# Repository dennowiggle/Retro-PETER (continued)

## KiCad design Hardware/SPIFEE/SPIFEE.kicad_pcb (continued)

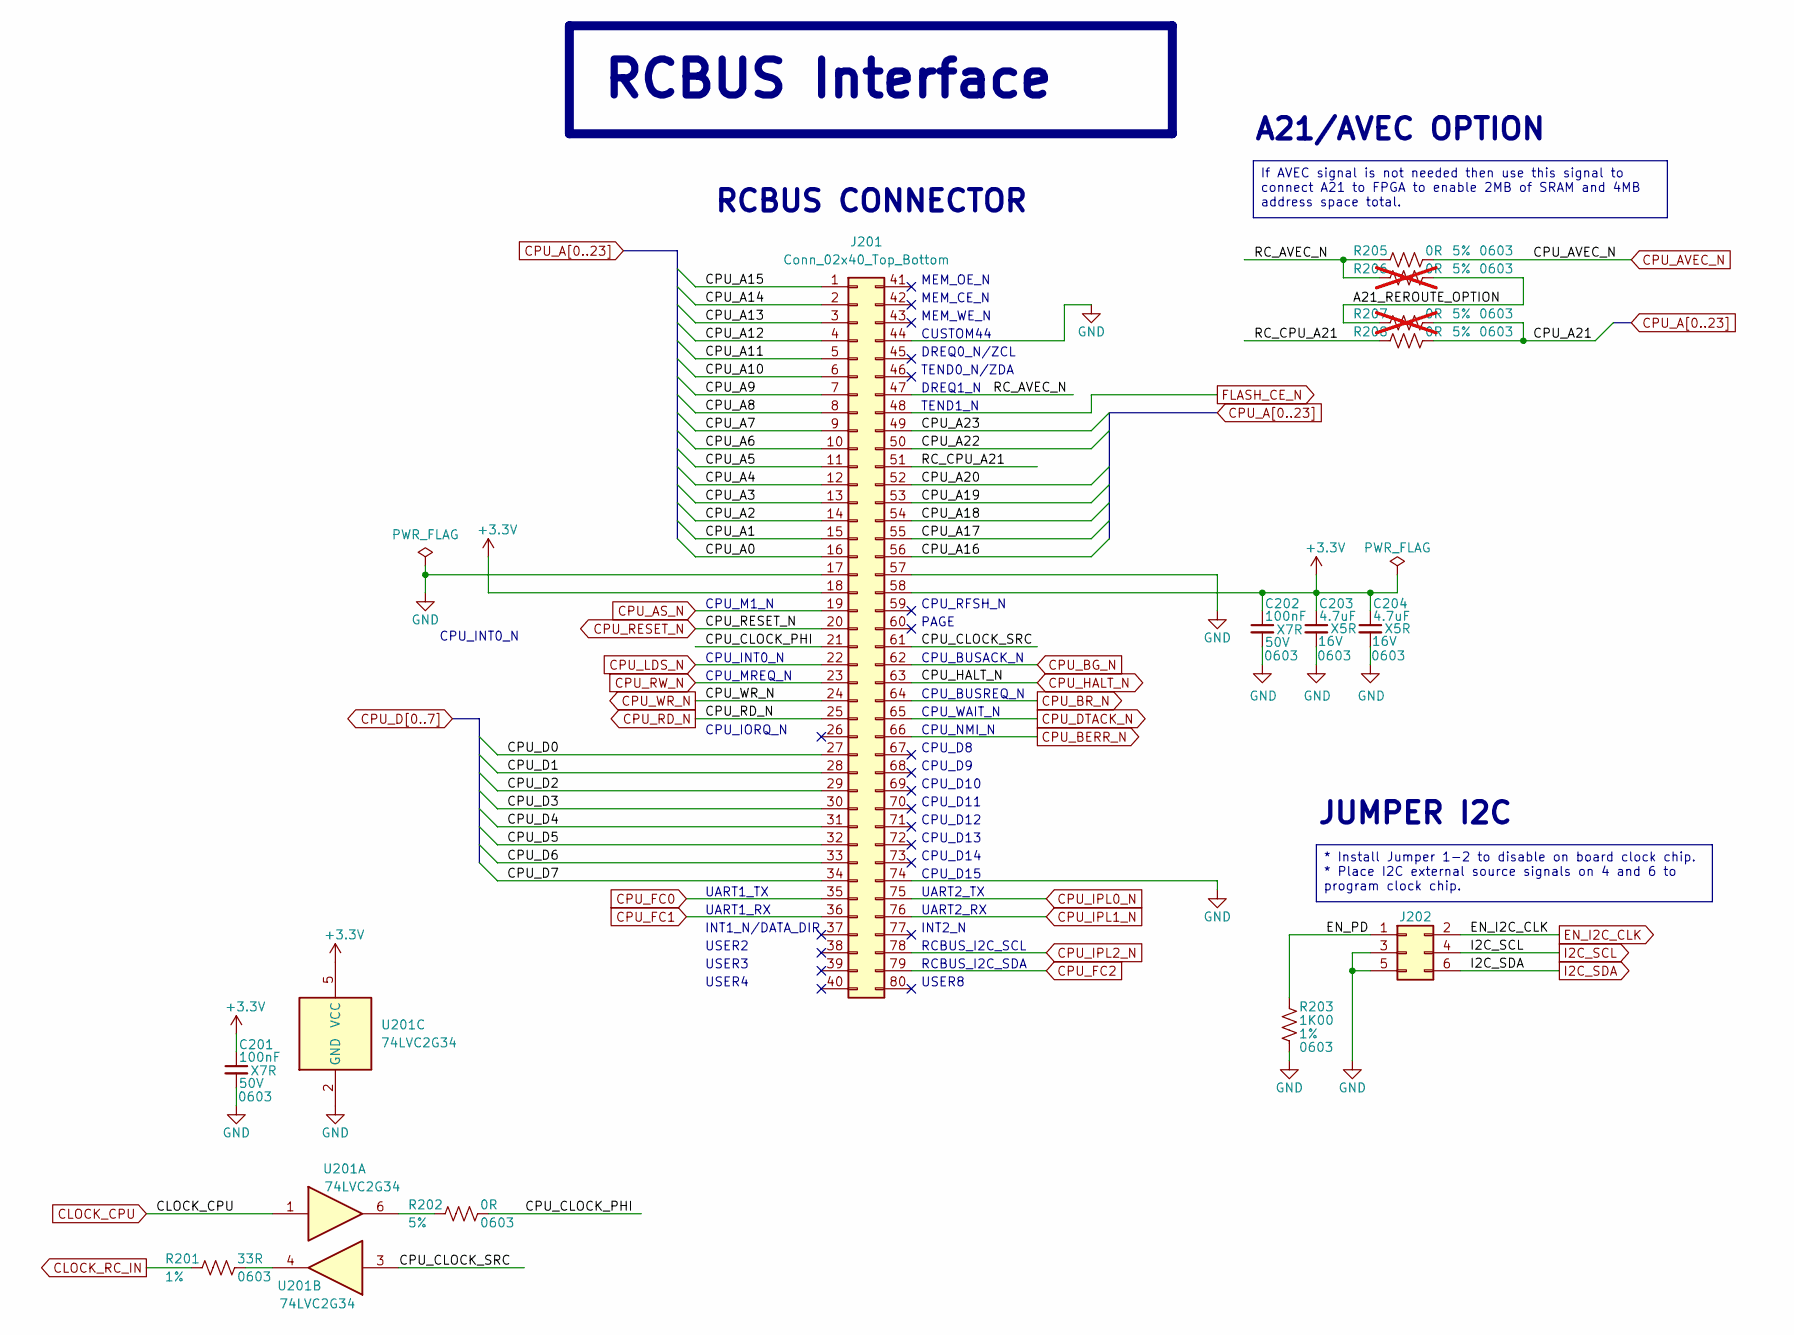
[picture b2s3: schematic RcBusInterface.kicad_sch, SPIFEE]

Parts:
C201, C202: 100nF; C_0603_1608Metric; Voltage 50V; Tolerance 10%; MPN CC0603KRX7R9BB104; Digikey 311-1344-1-ND
C203, C204: 4.7uF; C_0603_1608Metric; Voltage 16V; Tolerance 10%; MPN CL10A475KO8NNNC; Digikey 1276-1784-1-ND
J201: Conn_02x40_Top_Bottom; RCBUS_PinHeader_2x40_P2.54mm_Horizontal; MPN PH2RA-80-UA; Digikey 2057-PH2RA-80-UA-ND
J202: Conn_02x03; PinHeader_2x03_P2.54mm_Vertical; MPN PH2-06-UA; Digikey 2057-PH2-06-UA-ND
R201: 33R; R_0603_1608Metric; Tolerance 1%; MPN RC0603FR-0733RL; Digikey 13-RC0603FR-0733RLCT-ND
R202, R205, R208: 0R; R_0603_1608Metric; Tolerance 5%; MPN RC0603JR-070RL; Digikey 311-0.0GRCT-ND
R203: 1K00; R_0603_1608Metric; Tolerance 1%; MPN RC0603FR-071KL; Digikey 311-1.00KHRCT-ND
R206, R207: 0R; R_0603_1608Metric; Tolerance 5%; MPN RC0603JR-070RL; Digikey 311-0.0GRCT-ND; not fitted
U201: 74LVC2G34; SOT-363_SC-70-6; MPN 74LVC2G34GW,125; Digikey 1727-4219-1-ND

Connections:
+3.3V: C201.1, C202.1, C203.1, C204.1, J201.18, J201.58, U201.5 (VCC); also elsewhere on the board
/RcBusInterface/A21_REROUTE_OPTION: R206.2, R207.1
/RcBusInterface/CPU_CLOCK_PHI: J201.21, R202.2
/RcBusInterface/CPU_CLOCK_SRC: J201.61, U201.3
/RcBusInterface/EN_PD: J202.1, R203.1
/RcBusInterface/RC_AVEC_N: J201.47, R205.1, R206.1
/RcBusInterface/RC_CPU_A21: J201.51, R208.1
CLOCK_CPU: U201.1; also elsewhere on the board
CLOCK_RC_IN: R201.1; also elsewhere on the board
CPU_A0: J201.16; also elsewhere on the board
CPU_A1: J201.15; also elsewhere on the board
CPU_A2: J201.14; also elsewhere on the board
CPU_A3: J201.13; also elsewhere on the board
CPU_A4: J201.12; also elsewhere on the board
CPU_A5: J201.11; also elsewhere on the board
CPU_A6: J201.10; also elsewhere on the board
CPU_A7: J201.9; also elsewhere on the board
CPU_A8: J201.8; also elsewhere on the board
CPU_A9: J201.7; also elsewhere on the board
CPU_A10: J201.6; also elsewhere on the board
CPU_A11: J201.5; also elsewhere on the board
CPU_A12: J201.4; also elsewhere on the board
CPU_A13: J201.3; also elsewhere on the board
CPU_A14: J201.2; also elsewhere on the board
CPU_A15: J201.1; also elsewhere on the board
CPU_A16: J201.56; also elsewhere on the board
CPU_A17: J201.55; also elsewhere on the board
CPU_A18: J201.54; also elsewhere on the board
CPU_A19: J201.53; also elsewhere on the board
CPU_A20: J201.52; also elsewhere on the board
CPU_A21: R207.2, R208.2; also elsewhere on the board
CPU_A22: J201.50; also elsewhere on the board
CPU_A23: J201.49; also elsewhere on the board
CPU_AS_N: J201.19; also elsewhere on the board
CPU_AVEC_N: R205.2; also elsewhere on the board
CPU_BERR_N: J201.66; also elsewhere on the board
CPU_BG_N: J201.62; also elsewhere on the board
CPU_BR_N: J201.64; also elsewhere on the board
CPU_D0: J201.27; also elsewhere on the board
CPU_D1: J201.28; also elsewhere on the board
CPU_D2: J201.29; also elsewhere on the board
CPU_D3: J201.30; also elsewhere on the board
CPU_D4: J201.31; also elsewhere on the board
CPU_D5: J201.32; also elsewhere on the board
CPU_D6: J201.33; also elsewhere on the board
CPU_D7: J201.34; also elsewhere on the board
CPU_DTACK_N: J201.65; also elsewhere on the board
CPU_FC0: J201.35; also elsewhere on the board
CPU_FC1: J201.36; also elsewhere on the board
CPU_FC2: J201.79; also elsewhere on the board
CPU_HALT_N: J201.63; also elsewhere on the board
CPU_IPL0_N: J201.75; also elsewhere on the board
CPU_IPL1_N: J201.76; also elsewhere on the board
CPU_IPL2_N: J201.78; also elsewhere on the board
CPU_LDS_N: J201.22; also elsewhere on the board
CPU_RD_N: J201.25; also elsewhere on the board
CPU_RESET_N: J201.20; also elsewhere on the board
CPU_RW_N: J201.23; also elsewhere on the board
CPU_WR_N: J201.24; also elsewhere on the board
EN_I2C_CLK: J202.2; also elsewhere on the board
FLASH_CE_N: J201.48; also elsewhere on the board
GND: C201.2, C202.2, C203.2, C204.2, J201.17, J201.44, J201.57, J201.74, J202.3, J202.5, R203.2, U201.2 (GND); also elsewhere on the board
I2C_SCL: J202.4; also elsewhere on the board
I2C_SDA: J202.6; also elsewhere on the board
unnamed: R201.2, U201.4
unnamed: R202.1, U201.6

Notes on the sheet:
MEM_OE_N
A21/AVEC OPTION
CPU_NMI_N
CPU_BUSACK_N
CPU_INT0_N
MEM_WE_N
CPU_RFSH_N
CPU_D11
RCBUS_I2C_SDA
RCBUS CONNECTOR
CPU_D15
TEND1_N
CPU_D8
CPU_D14
UART2_TX
CPU_D12
UART2_RX
USER2
INT2_N
USER4
JUMPER I2C
CPU_MREQ_N
USER3
CPU_M1_N
CPU_WAIT_N
RCBUS_I2C_SCL
TEND0_N/ZDA
INT1_N/DATA_DIR
MEM_CE_N
UART1_TX
CPU_D9
USER8
DREQ0_N/ZCL
UART1_RX
CPU_D13
PAGE
CPU_BUSREQ_N
CUSTOM44
DREQ1_N
CPU_IORQ_N

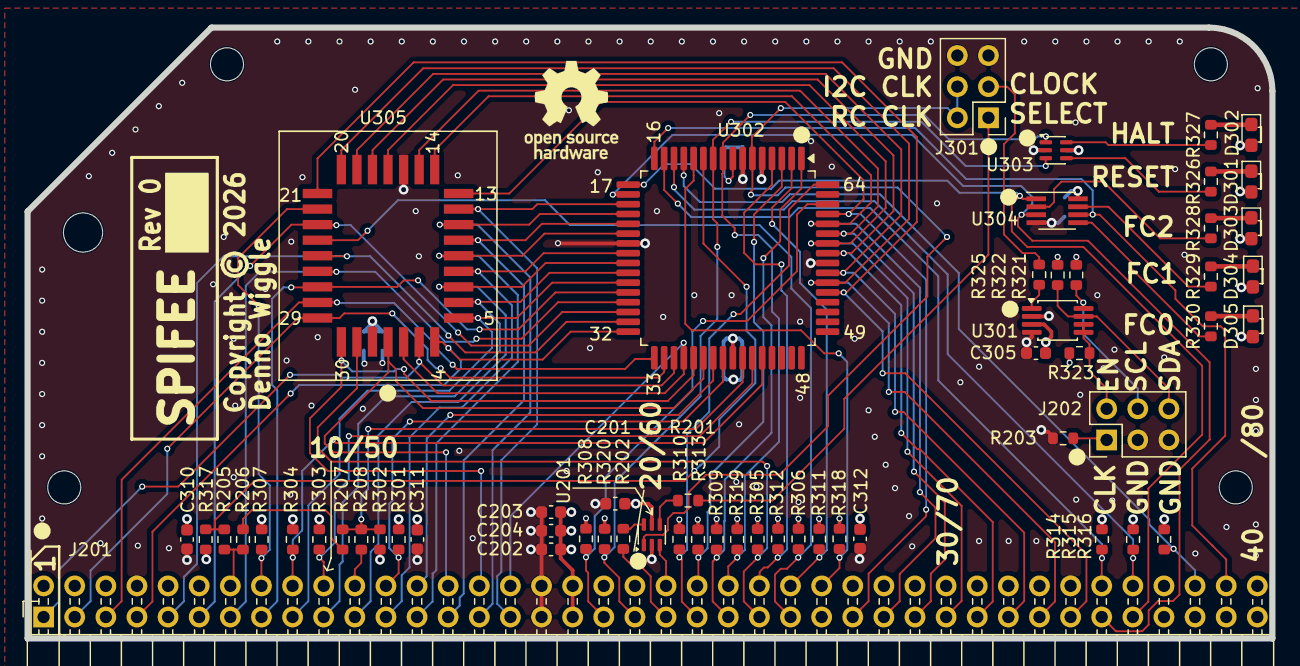
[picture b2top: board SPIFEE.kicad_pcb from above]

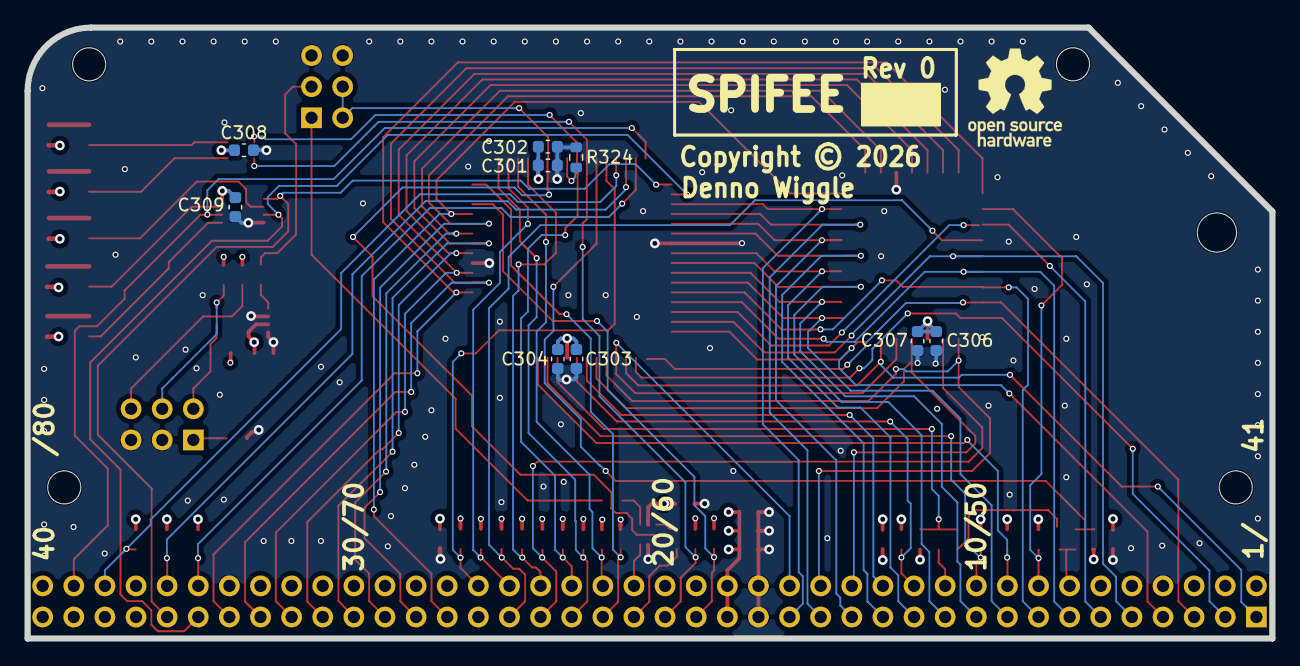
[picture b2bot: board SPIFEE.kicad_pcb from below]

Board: 4 copper layers, 101.6 x 49.9 mm, 74 parts (10 on the bottom side), 79 nets.

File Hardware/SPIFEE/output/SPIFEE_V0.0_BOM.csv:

"Reference","Value","Qty","DNP","Digikey","LCSC Part #","MPN","Manufacturer","Description"
"C201,C202,C301,C304,C305,C307,C308,C309,C310,C311,C312","100nF","11","","311-1344-1-ND","C14663","CC0603KRX7R9BB104","YAGEO","CAP CER 0.1UF 50V X7R 0603"
"R301,R302,R303,R304,R305,R306,R307,R308,R309,R310,R311,R312,R313,R314,R315,R316,R317,R318,R319,R320,R321,R322,R323","10K","23","","311-10.0KHRCT-ND","C98220","RC0603FR-0710KL","Yaego","RES 10K OHM 1% 1/10W 0603"
"R206,R207","0R","2","DNP","311-0.0GRCT-ND","C95177","RC0603JR-070RL","Yaego","RES 0 OHM 5% 1/10W 0603"
"R203,R326,R327,R328,R329,R330","1K00","6","","311-1.00KHRCT-ND","C22548","RC0603FR-071KL","Yaego","RES 1K OHM 1% 1/10W 0603"
"R202,R205,R208","0R","3","","311-0.0GRCT-ND","C95177","RC0603JR-070RL","Yaego","RES 0 OHM 5% 1/10W 0603"
"R201,R324,R325","33R","3","","13-RC0603FR-0733RLCT-ND","C108661","RC0603FR-0733RL","Yaego","RES 33 OHM 1% 1/10W 0603"
"C203,C204,C302,C303,C306","4.7uF","5","","1276-1784-1-ND","C19666","CL10A475KO8NNNC","Yaego","CAP CER 4.7UF 16V X5R 0603"
"U303","74LVC2G07","1","","1727-4121-1-ND","C24478","74LVC2G07GW,125","Nexperia","IC BUFF NON-INVERT 5.5V 6-TSSOP"
"U201","74LVC2G34","1","","1727-4219-1-ND","","74LVC2G34GW,125","Nexperia","IC BUFF NON-INVERT 5.5V 6-TSSOP"
"U302","MC68SEC000FU","1","","","","MC68SEC000FU20","Motorola","16/32-bit microprocessor, 16-bit external data bus, 23-bit external address bus (effectively 24-bit), QFP64"
"U305","SST39SF040-55","1","","SST39LF040-55-4C-NHE-ND","C645927","SST39LF040-55-4C-NHE","Microchip","IC FLASH 4MBIT 512KX8 PARALLEL 3V3 55ns PLCC32"
"D301,D302,D303,D304,D305","LED_LTST-S270KGKT","5","","160-1478-1-ND","C125113","LTST-S270KGKT","Lite-On Inc.","LED 571NM GREEN CLEAR CHIP 0603 R/A"
"U304","74LVC3G06","1","","31-74LVC3G06SS8-7CT-ND","C6089410","74LVC3G06SS8-7","Diodes Incorporated","IC INVERTER 3CH 3-INP 8SSOP"
"U301","DS1086LU+","1","","DS1086LU+-ND","C1519863","DS1086LU+","Analog Devices Inc./Maxim Integrated","IC I2C SS CLOCK GENERATOR uSOP8"
"J202,J301","Conn_02x03","2","","2057-PH2-06-UA-ND","","PH2-06-UA","Adam Tech","CONN HEADER VERT 6POS 2.54MM"
"J201","Conn_02x40_Top_Bottom","1","","2057-PH2RA-80-UA-ND","","PH2RA-80-UA","Adam Tech","CONN HEADER R/A 80POS 2.54MM"
"H1,H2,H3,H4,H5","MountingHole","5","","","","","",""

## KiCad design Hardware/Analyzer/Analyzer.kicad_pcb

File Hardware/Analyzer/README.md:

# ANALYZER
72 channel logic analyzer for RCBUS.

## Description
ANALYZER is a 72 channel logic analyzer in an RCBUS board form factor with 3 x Pi Pico modules. 

This design is a derivative work of John Winans [S-100 bus logic analyzer](https://github.com/johnwinans/2070-S-100-bus-analyzer) targeted for RCBUS instead of S-100 bus for use on the PETER project.

Both projects use the Dr Gusman [LogicAnalyzer software and firmware](https://github.com/gusmanb/logicanalyzer).

## Top View

## Bottom View

## ANALYZER Board Rev 0.0 Release Notes

1. The 'output' directory contains the BOM, netlist, and PDF schematic.

2. Board design used KiCad 10.0

3. Use sockets to mount the PICO's so that they are elevated above the board for anyone wanting to try WiFi.

## Notes for future
1. Consider using 3 x individual Pico 10K pull-down resistors for
  - TRIG_CHA, TRIG_CHB, TRIG_CHC instead of R302 2.2K on TRIG.

2. Consider replacing D201 with 3 schottky diodes to VSYS_A, VSYS_B, VSYS_B.
  - Provides option for manually sequencing power via each Pico USB connector.
  - Useful for getting same tty device name in Linux on each power on.

## Analyzer Board Pi Pico Channel Mapping to Signal and Pin Names
The [gusmanb software](https://github.com/gusmanb/logicanalyzer) only has the choice of 16 pins for trigger.

The table below has the middle PICO as the master. With the RCBUS backplane you can jumper the desired trigger signal to one of the unused pins. e.g. custom pin 41, analyzer channel 1.

 | Pico A       | Single A | Multi A | PETER Signal | RCBUS Pin | RCBUS Name  | 
 | ------------ | -------- | ------- | ------------ | --------- | ----------- |
 | GPIO_CHA_P2  | 1        | 25      | A15          | 1         | A15         | 
 | GPIO_CHA_P3  | 2        | 26      | A14          | 2         | A14         | 
 | GPIO_CHA_P4  | 3        | 27      | A13          | 3         | A13         | 
 | GPIO_CHA_P5  | 4        | 28      | DREQ0_N      | 45        | custom      | 
 | GPIO_CHA_P6  | 5        | 29      | A11          | 5         | A11         | 
 | GPIO_CHA_P7  | 6        | 30      | A10          | 6         | A10         | 
 | GPIO_CHA_P8  | 7        | 31      | A5           | 11        | A5          | 
 | GPIO_CHA_P9  | 8        | 32      | A21          | 51        | A21         | 
 | GPIO_CHA_P10 | 9        | 33      | A6           | 10        | A6          | 
 | GPIO_CHA_P11 | 10       | 34      | A22          | 50        | A22         | 
 | GPIO_CHA_P12 | 11       | 35      | A7           | 9         | A7          | 
 | GPIO_CHA_P13 | 12       | 36      | A23          | 49        | A23         | 
 | GPIO_CHA_P14 | 13       | 37      | A9           | 7         | A9          | 
 | GPIO_CHA_P15 | 14       | 38      | A8           | 8         | A8          | 
 | GPIO_CHA_P16 | 15       | 39      | A2           | 14        | A2          | 
 | GPIO_CHA_P17 | 16       | 40      | A17          | 55        | A17         | 
 | GPIO_CHA_P18 | 17       | 41      | A1           | 15        | A1          | 
 | GPIO_CHA_P19 | 18       | 42      | A16          | 56        | A16         | 
 | GPIO_CHA_P20 | 19       | 43      | A0           | 16        | A0          | 
 | GPIO_CHA_P21 | 20       | 44      | A18          | 54        | A18         | 
 | GPIO_CHA_P22 | 21       | 45      | A3           | 13        | A3          | 
 | GPIO_CHA_A0  | 22       | 46      | A19          | 53        | A19         | 
 | GPIO_CHA_A1  | 23       | 47      | A4           | 12        | A4          | 
 | GPIO_CHA_A2  | 24       | 48      | A20          | 52        | A20         | 
 
 | Pico B       | Single B | Multi B | PETER Signal | RCBUS Pin | RCBUS Name  | 
 | ------------ | -------- | ------- | ------------ | --------- | ----------- |
 | GPIO_CHB_P2  | 1        | 1       | MEM_OE_N     | 41        | custom      | 
 | GPIO_CHB_P3  | 2        | 2       | MEM_CE_N     | 42        | custom      | 
 | GPIO_CHB_P4  | 3        | 3       | MEM_WE_N     | 43        | custom      | 
 | GPIO_CHB_P5  | 4        | 4       | A12          | 4         | A12         | 
 | GPIO_CHB_P6  | 5        | 5       | TEND0_N      | 46        | custom      | 
 | GPIO_CHB_P7  | 6        | 6       | DREQ1_N      | 47        | custom      | 
 | GPIO_CHB_P8  | 7        | 7       | TEND1_N      | 48        | custom      | 
 | GPIO_CHB_P9  | 8        | 8       | M1_N         | 19        | /M1         | 
 | GPIO_CHB_P10 | 9        | 9       | BUSACK_N     | 62        | /BUSAK      | 
 | GPIO_CHB_P11 | 10       | 10      | INT0_N       | 22        | /INT        | 
 | GPIO_CHB_P12 | 11       | 11      | CLK_SRC      | 61        | CLK2        | 
 | GPIO_CHB_P13 | 12       | 12      | CLK_PHI      | 21        | CLK         | 
 | GPIO_CHB_P14 | 13       | 13      | PAGE         | 60        | PAGE_RESET2 | 
 | GPIO_CHB_P15 | 14       | 14      | RESET_N      | 20        | /RESET      | 
 | GPIO_CHB_P16 | 15       | 15      | WAIT_N       | 65        | /WAIT       | 
 | GPIO_CHB_P17 | 16       | 16      | RD_N         | 25        | /RD         | 
 | GPIO_CHB_P18 | 17       | 17      | BUSREQ_N     | 64        | /BUSRQ      | 
 | GPIO_CHB_P19 | 18       | 18      | WR_N         | 24        | /WR         | 
 | GPIO_CHB_P20 | 19       | 19      | HALT_N       | 63        | /HALT       | 
 | GPIO_CHB_P21 | 20       | 20      | MREQ_N       | 23        | /MREQ       | 
 | GPIO_CHB_P22 | 21       | 21      | IORQ_N       | 26        | /IORQ       | 
 | GPIO_CHB_A0  | 22       | 22      | NMI_N        | 66        | /NMI        | 
 | GPIO_CHB_A1  | 23       | 23      | I2C_SCL      | 78        | USER6       | 
 | GPIO_CHB_A2  | 24       | 24      | I2C_SDA      | 79        | USER7       | 
 
 | Pico C       | Single C | Multi C | PETER Signal | RCBUS Pin | RCBUS Name  | 
 | ------------ | -------- | ------- | ------------ | --------- | ----------- |
 | GPIO_CHC_P2  | 1        | 49      | D0           | 27        | D0          | 
 | GPIO_CHC_P3  | 2        | 50      | D8           | 67        | D8          | 
 | GPIO_CHC_P4  | 3        | 51      | D1           | 28        | D1          | 
 | GPIO_CHC_P5  | 4        | 52      | D9           | 68        | D9          | 
 | GPIO_CHC_P6  | 5        | 53      | D2           | 29        | D2          | 
 | GPIO_CHC_P7  | 6        | 54      | D10          | 69        | D10         | 
 | GPIO_CHC_P8  | 7        | 55      | D3           | 30        | D3          | 
 | GPIO_CHC_P9  | 8        | 56      | D11          | 70        | D11         | 
 | GPIO_CHC_P10 | 9        | 57      | D14          | 73        | D14         | 
 | GPIO_CHC_P11 | 10       | 58      | D6           | 33        | D6          | 
 | GPIO_CHC_P12 | 11       | 59      | D13          | 72        | D13         | 
 | GPIO_CHC_P13 | 12       | 60      | D5           | 32        | D5          | 
 | GPIO_CHC_P14 | 13       | 61      | D12          | 71        | D12         | 
 | GPIO_CHC_P15 | 14       | 62      | D4           | 31        | D4          | 
 | GPIO_CHC_P16 | 15       | 63      | UART1_RX     | 36        | RX          | 
 | GPIO_CHC_P17 | 16       | 64      | UART2_TX     | 75        | TX2         | 
 | GPIO_CHC_P18 | 17       | 65      | UART1_TX     | 35        | TX          | 
 | GPIO_CHC_P19 | 18       | 66      | D15          | 74        | D15         | 
 | GPIO_CHC_P20 | 19       | 67      | D7           | 34        | D7          | 
 | GPIO_CHC_P21 | 20       | 68      | UART2_RX     | 76        | RX2         | 
 | GPIO_CHC_P22 | 21       | 69      | DATA_DIR     | 37        | USER1       | 
 | GPIO_CHC_A0  | 22       | 70      | USER2        | 38        | USER2       | 
 | GPIO_CHC_A1  | 23       | 71      | USER3        | 39        | USER3       | 
 | GPIO_CHC_A2  | 24       | 72      | USER4        | 40        | USER4       | 

 | Unconnected  |          |         |              | RCBUS Pin | RCBUS Name  | 
 | ------------ | -------- | ------- | ------------ | --------- | ----------- |
 |              |          |         |              | 57        | GND         | 
 |              |          |         |              | 58        | 5V          | 
 |              |          |         |              | 59        | /RFSH       | 
 |              |          |         |              | 77        | USER5       | 
 |              |          |         |              | 80        | USER8_IEI   |

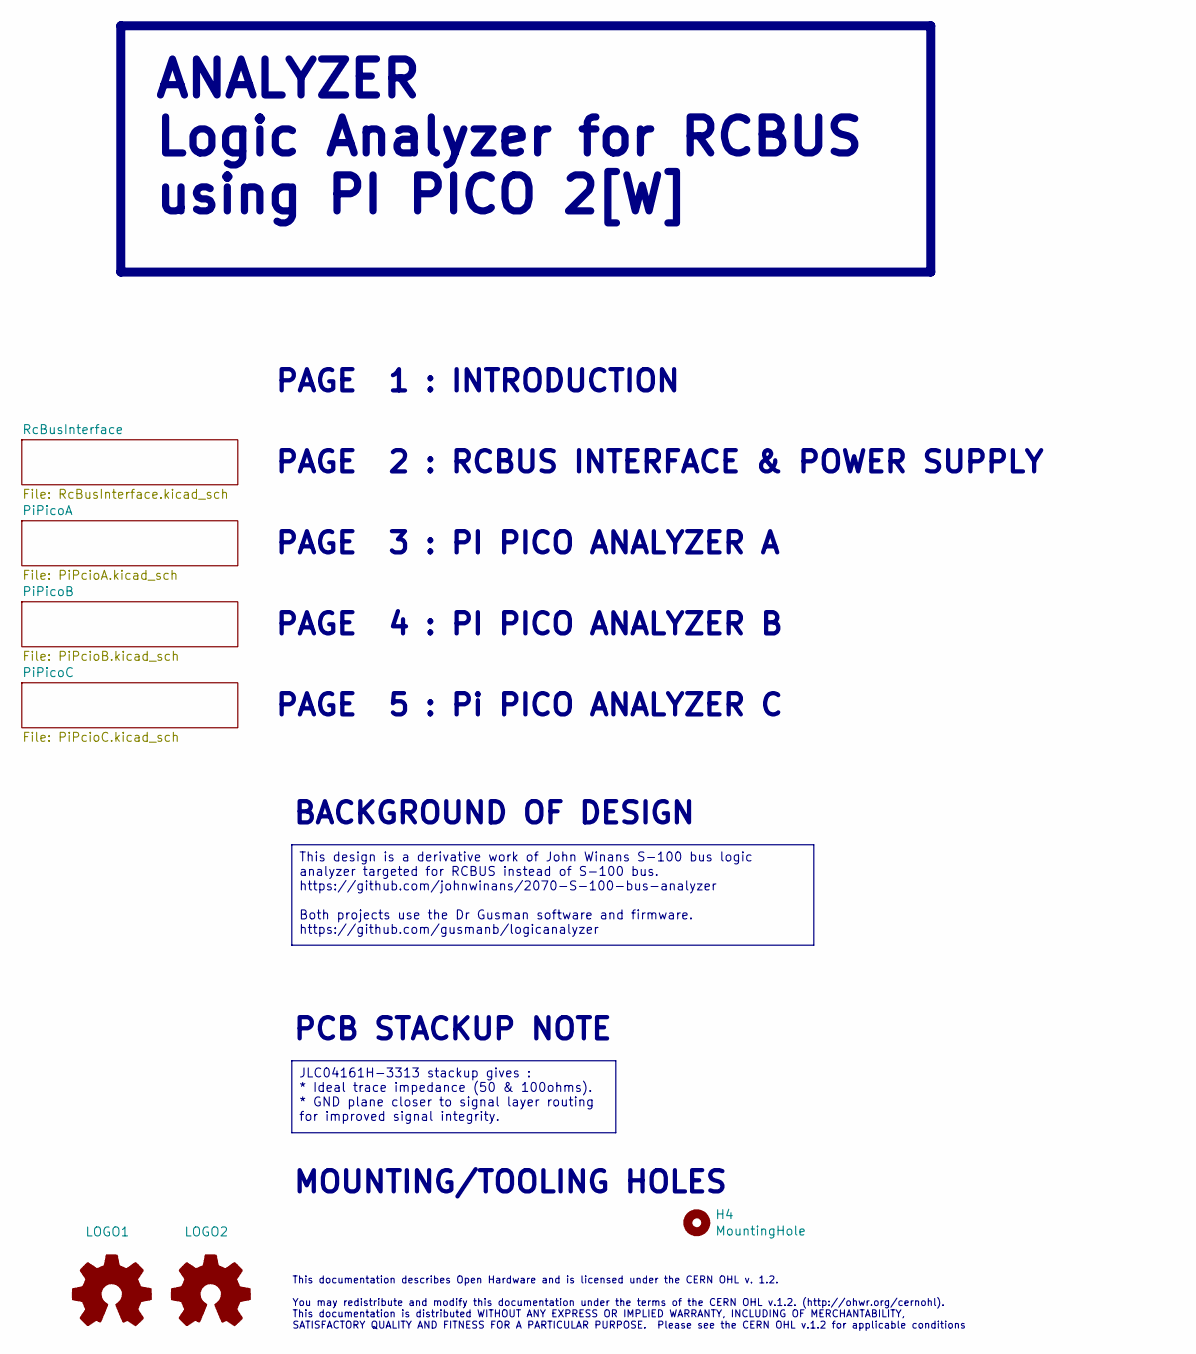
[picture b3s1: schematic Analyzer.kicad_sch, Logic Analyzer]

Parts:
H4: MountingHole; MountingHole_2.7mm_M2.5_DIN965
LOGO1, LOGO2: Logo_Open_Hardware_Small; OSHW-Logo_7.5x8mm_SilkScreen

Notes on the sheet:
MOUNTING/TOOLING HOLES
PAGE 4 : PI PICO ANALYZER B
PAGE 1 : INTRODUCTION
PCB STACKUP NOTE
This documentation describes Open Hardware and is licensed under the CERN OHL v. 1.2. You may redistribute and modify this documentation under the terms of the CERN OHL v.1.2. (http://ohwr.org/cernohl). This documentation is distributed WITHOUT ANY EXPRESS OR IMPLIED WARRANTY, INCLUDING OF MERCHANT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
PAGE 3 : PI PICO ANALYZER A
PAGE 5 : Pi PICO ANALYZER C
PAGE 2 : RCBUS INTERFACE & POWER SUPPLY
BACKGROUND OF DESIGN
This design is a derivative work of John Winans S-100 bus logic analyzer targeted for RCBUS instead of S-100 bus. https://github.com/johnwinans/2070-S-100-bus-analyzer Both projects use the Dr Gusman software and firmware. https://github.com/gusmanb/logicanalyzer
JLC04161H-3313 stackup gives : * Ideal trace impedance (50 & 100ohms). * GND plane closer to signal layer routing for improved signal integrity.
ANALYZER Logic Analyzer for RCBUS using PI PICO 2[W]

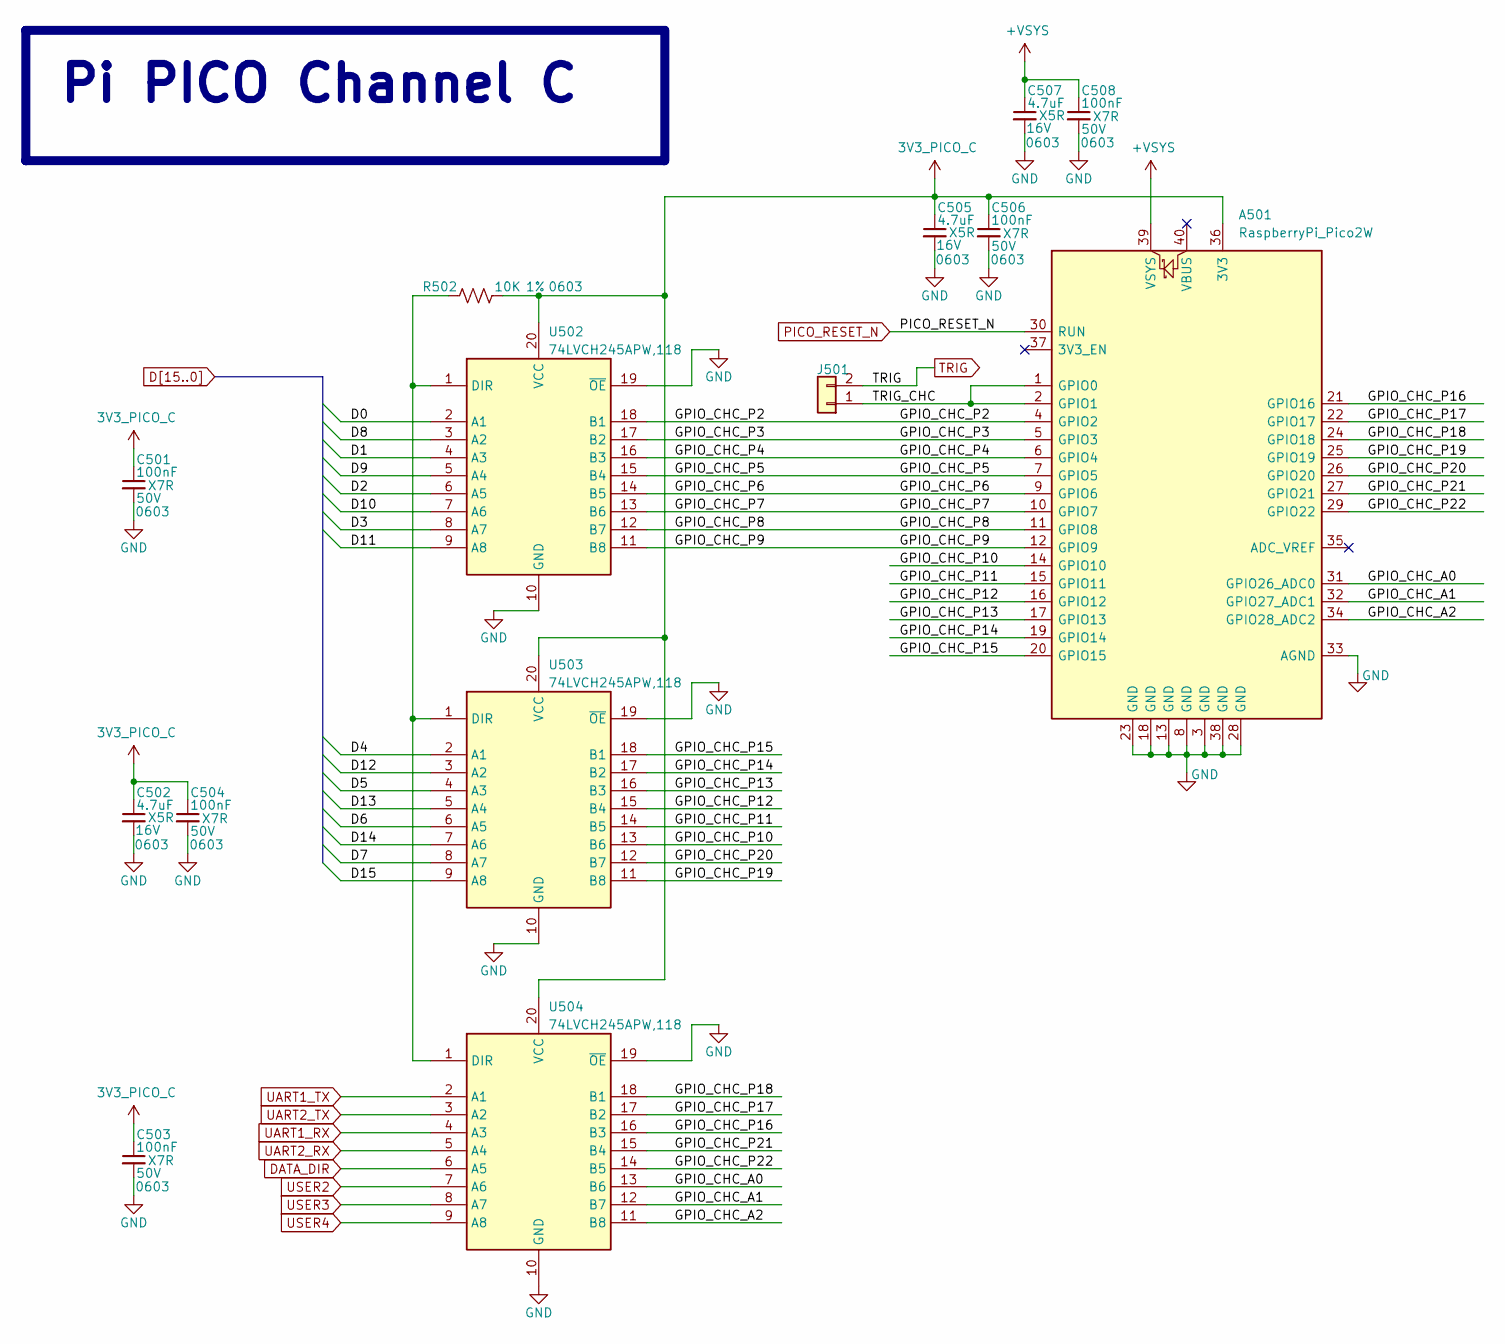
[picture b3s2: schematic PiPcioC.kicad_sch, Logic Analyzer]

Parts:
A501: RaspberryPi_Pico2W; RaspberryPi_Pico_Common_THT; MPN SC1634; Digikey 2648-SC1634-ND
C501, C503, C504, C506, C508: 100nF; C_0603_1608Metric; Voltage 50V; Tolerance 10%; MPN CC0603KRX7R9BB104; Digikey 311-1344-1-ND
C502, C505, C507: 4.7uF; C_0603_1608Metric; Voltage 16V; Tolerance 10%; MPN CL10A475KO8NNNC; Digikey 1276-1784-1-ND
J501: Conn_01x02; PinHeader_1x02_P2.54mm_Vertical; MPN PH2-02-UA; Digikey 2057-PH2-02-UA-ND
R502: 10K; R_0603_1608Metric; Tolerance 1%; MPN RC0603FR-0710KL; Digikey 311-10.0KHRCT-ND
U502, U503, U504: 74LVCH245APW,118; TSSOP-20_4.4x6.5mm_P0.65mm; MPN 74LVCH245APW,118; Digikey 1727-4041-1-ND

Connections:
3V3_PICO_C: A501.36 (3V3), C501.1, C502.1, C503.1, C504.1, C505.1, C506.1, R502.2, U502.20 (VCC), U503.20 (VCC), U504.20 (VCC)
+VSYS: A501.39 (VSYS), C507.1, C508.1; also elsewhere on the board
/PiPicoC/GPIO_CHC_A0: A501.31 (GPIO26_ADC0), U504.13 (B6)
/PiPicoC/GPIO_CHC_A1: A501.32 (GPIO27_ADC1), U504.12 (B7)
/PiPicoC/GPIO_CHC_A2: A501.34 (GPIO28_ADC2), U504.11 (B8)
/PiPicoC/GPIO_CHC_P2: A501.4 (GPIO2), U502.18 (B1)
/PiPicoC/GPIO_CHC_P3: A501.5 (GPIO3), U502.17 (B2)
/PiPicoC/GPIO_CHC_P4: A501.6 (GPIO4), U502.16 (B3)
/PiPicoC/GPIO_CHC_P5: A501.7 (GPIO5), U502.15 (B4)
/PiPicoC/GPIO_CHC_P6: A501.9 (GPIO6), U502.14 (B5)
/PiPicoC/GPIO_CHC_P7: A501.10 (GPIO7), U502.13 (B6)
/PiPicoC/GPIO_CHC_P8: A501.11 (GPIO8), U502.12 (B7)
/PiPicoC/GPIO_CHC_P9: A501.12 (GPIO9), U502.11 (B8)
/PiPicoC/GPIO_CHC_P10: A501.14 (GPIO10), U503.13 (B6)
/PiPicoC/GPIO_CHC_P11: A501.15 (GPIO11), U503.14 (B5)
/PiPicoC/GPIO_CHC_P12: A501.16 (GPIO12), U503.15 (B4)
/PiPicoC/GPIO_CHC_P13: A501.17 (GPIO13), U503.16 (B3)
/PiPicoC/GPIO_CHC_P14: A501.19 (GPIO14), U503.17 (B2)
/PiPicoC/GPIO_CHC_P15: A501.20 (GPIO15), U503.18 (B1)
/PiPicoC/GPIO_CHC_P16: A501.21 (GPIO16), U504.16 (B3)
/PiPicoC/GPIO_CHC_P17: A501.22 (GPIO17), U504.17 (B2)
/PiPicoC/GPIO_CHC_P18: A501.24 (GPIO18), U504.18 (B1)
/PiPicoC/GPIO_CHC_P19: A501.25 (GPIO19), U503.11 (B8)
/PiPicoC/GPIO_CHC_P20: A501.26 (GPIO20), U503.12 (B7)
/PiPicoC/GPIO_CHC_P21: A501.27 (GPIO21), U504.15 (B4)
/PiPicoC/GPIO_CHC_P22: A501.29 (GPIO22), U504.14 (B5)
/PiPicoC/TRIG_CHC: A501.1 (GPIO0), A501.2 (GPIO1), J501.1
D0: U502.2 (A1); also elsewhere on the board
D1: U502.4 (A3); also elsewhere on the board
D2: U502.6 (A5); also elsewhere on the board
D3: U502.8 (A7); also elsewhere on the board
D4: U503.2 (A1); also elsewhere on the board
D5: U503.4 (A3); also elsewhere on the board
D6: U503.6 (A5); also elsewhere on the board
D7: U503.8 (A7); also elsewhere on the board
D8: U502.3 (A2); also elsewhere on the board
D9: U502.5 (A4); also elsewhere on the board
D10: U502.7 (A6); also elsewhere on the board
D11: U502.9 (A8); also elsewhere on the board
D12: U503.3 (A2); also elsewhere on the board
D13: U503.5 (A4); also elsewhere on the board
D14: U503.7 (A6); also elsewhere on the board
D15: U503.9 (A8); also elsewhere on the board
DATA_DIR: U504.6 (A5); also elsewhere on the board
GND: A501.3 (GND), A501.8 (GND), A501.13 (GND), A501.18 (GND), A501.23 (GND), A501.28 (GND), A501.33 (AGND), A501.38 (GND), C501.2, C502.2, C503.2, C504.2, C505.2, C506.2, C507.2, C508.2, U502.10 (GND), U502.19 (~OE), U503.10 (GND), U503.19 (~OE), U504.10 (GND), U504.19 (~OE); also elsewhere on the board
unnamed: R502.1, U502.1 (DIR), U503.1 (DIR), U504.1 (DIR)
PICO_RESET_N: A501.30 (RUN); also elsewhere on the board
TRIG: J501.2; also elsewhere on the board
UART1_RX: U504.4 (A3); also elsewhere on the board
UART1_TX: U504.2 (A1); also elsewhere on the board
UART2_RX: U504.5 (A4); also elsewhere on the board
UART2_TX: U504.3 (A2); also elsewhere on the board
USER2: U504.7 (A6); also elsewhere on the board
USER3: U504.8 (A7); also elsewhere on the board
USER4: U504.9 (A8); also elsewhere on the board

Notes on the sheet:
Pi PICO Channel C

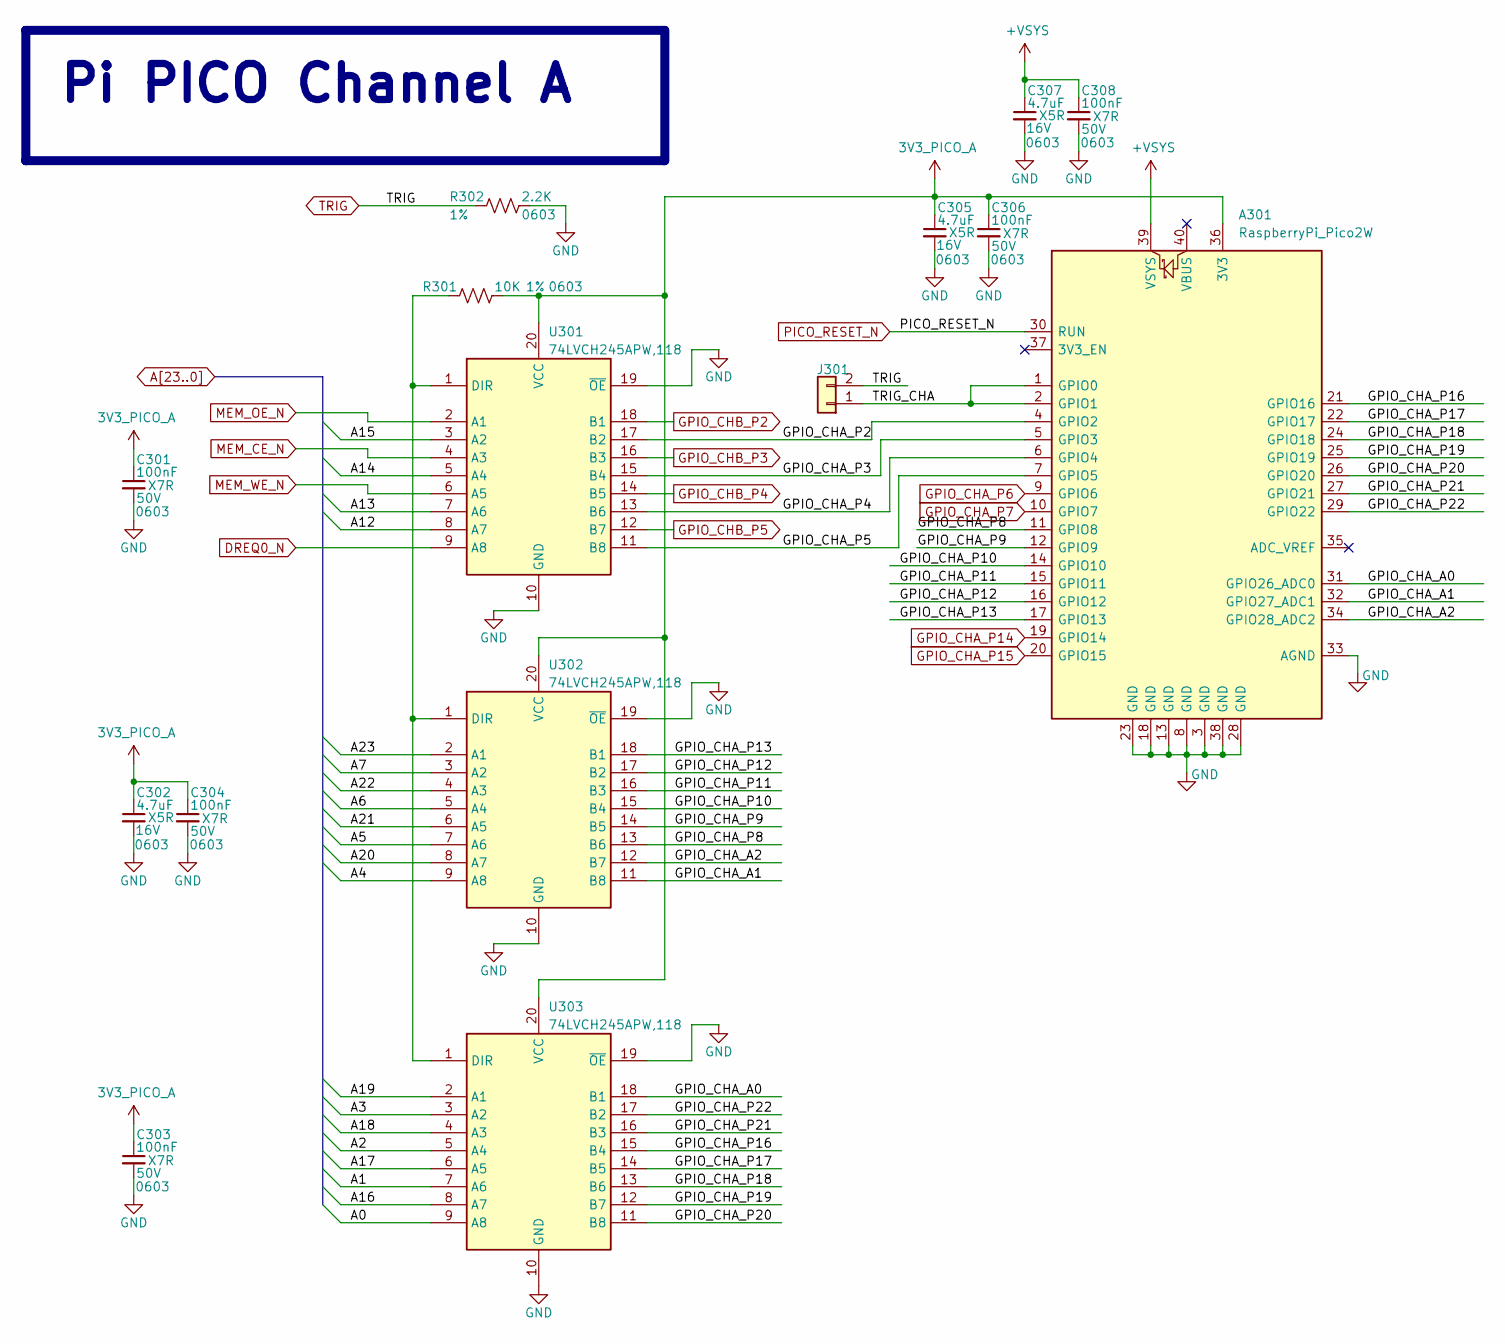
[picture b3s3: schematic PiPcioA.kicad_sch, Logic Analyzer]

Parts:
A301: RaspberryPi_Pico2W; RaspberryPi_Pico_Common_THT; MPN SC1634; Digikey 2648-SC1634-ND
C301, C303, C304, C306, C308: 100nF; C_0603_1608Metric; Voltage 50V; Tolerance 10%; MPN CC0603KRX7R9BB104; Digikey 311-1344-1-ND
C302, C305, C307: 4.7uF; C_0603_1608Metric; Voltage 16V; Tolerance 10%; MPN CL10A475KO8NNNC; Digikey 1276-1784-1-ND
J301: Conn_01x02; PinHeader_1x02_P2.54mm_Vertical; MPN PH2-02-UA; Digikey 2057-PH2-02-UA-ND
R301: 10K; R_0603_1608Metric; Tolerance 1%; MPN RC0603FR-0710KL; Digikey 311-10.0KHRCT-ND
R302: 2.2K; R_0603_1608Metric; Tolerance 1%; MPN RC0603FR-072K2L; Digikey 311-2.20KHRCT-ND
U301, U302, U303: 74LVCH245APW,118; TSSOP-20_4.4x6.5mm_P0.65mm; MPN 74LVCH245APW,118; Digikey 1727-4041-1-ND

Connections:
3V3_PICO_A: A301.36 (3V3), C301.1, C302.1, C303.1, C304.1, C305.1, C306.1, R301.2, U301.20 (VCC), U302.20 (VCC), U303.20 (VCC)
+VSYS: A301.39 (VSYS), C307.1, C308.1; also elsewhere on the board
/PiPicoA/GPIO_CHA_A0: A301.31 (GPIO26_ADC0), U303.18 (B1)
/PiPicoA/GPIO_CHA_A1: A301.32 (GPIO27_ADC1), U302.11 (B8)
/PiPicoA/GPIO_CHA_A2: A301.34 (GPIO28_ADC2), U302.12 (B7)
/PiPicoA/GPIO_CHA_P2: A301.4 (GPIO2), U301.17 (B2)
/PiPicoA/GPIO_CHA_P3: A301.5 (GPIO3), U301.15 (B4)
/PiPicoA/GPIO_CHA_P4: A301.6 (GPIO4), U301.13 (B6)
/PiPicoA/GPIO_CHA_P5: A301.7 (GPIO5), U301.11 (B8)
/PiPicoA/GPIO_CHA_P8: A301.11 (GPIO8), U302.13 (B6)
/PiPicoA/GPIO_CHA_P9: A301.12 (GPIO9), U302.14 (B5)
/PiPicoA/GPIO_CHA_P10: A301.14 (GPIO10), U302.15 (B4)
/PiPicoA/GPIO_CHA_P11: A301.15 (GPIO11), U302.16 (B3)
/PiPicoA/GPIO_CHA_P12: A301.16 (GPIO12), U302.17 (B2)
/PiPicoA/GPIO_CHA_P13: A301.17 (GPIO13), U302.18 (B1)
/PiPicoA/GPIO_CHA_P16: A301.21 (GPIO16), U303.15 (B4)
/PiPicoA/GPIO_CHA_P17: A301.22 (GPIO17), U303.14 (B5)
/PiPicoA/GPIO_CHA_P18: A301.24 (GPIO18), U303.13 (B6)
/PiPicoA/GPIO_CHA_P19: A301.25 (GPIO19), U303.12 (B7)
/PiPicoA/GPIO_CHA_P20: A301.26 (GPIO20), U303.11 (B8)
/PiPicoA/GPIO_CHA_P21: A301.27 (GPIO21), U303.16 (B3)
/PiPicoA/GPIO_CHA_P22: A301.29 (GPIO22), U303.17 (B2)
/PiPicoA/TRIG_CHA: A301.1 (GPIO0), A301.2 (GPIO1), J301.1
A0: U303.9 (A8); also elsewhere on the board
A1: U303.7 (A6); also elsewhere on the board
A2: U303.5 (A4); also elsewhere on the board
A3: U303.3 (A2); also elsewhere on the board
A4: U302.9 (A8); also elsewhere on the board
A5: U302.7 (A6); also elsewhere on the board
A6: U302.5 (A4); also elsewhere on the board
A7: U302.3 (A2); also elsewhere on the board
A12: U301.8 (A7); also elsewhere on the board
A13: U301.7 (A6); also elsewhere on the board
A14: U301.5 (A4); also elsewhere on the board
A15: U301.3 (A2); also elsewhere on the board
A16: U303.8 (A7); also elsewhere on the board
A17: U303.6 (A5); also elsewhere on the board
A18: U303.4 (A3); also elsewhere on the board
A19: U303.2 (A1); also elsewhere on the board
A20: U302.8 (A7); also elsewhere on the board
A21: U302.6 (A5); also elsewhere on the board
A22: U302.4 (A3); also elsewhere on the board
A23: U302.2 (A1); also elsewhere on the board
DREQ0_N: U301.9 (A8); also elsewhere on the board
GND: A301.3 (GND), A301.8 (GND), A301.13 (GND), A301.18 (GND), A301.23 (GND), A301.28 (GND), A301.33 (AGND), A301.38 (GND), C301.2, C302.2, C303.2, C304.2, C305.2, C306.2, C307.2, C308.2, R302.2, U301.10 (GND), U301.19 (~OE), U302.10 (GND), U302.19 (~OE), U303.10 (GND), U303.19 (~OE); also elsewhere on the board
GPIO_CHA_P6: A301.9 (GPIO6); also elsewhere on the board
GPIO_CHA_P7: A301.10 (GPIO7); also elsewhere on the board
GPIO_CHA_P14: A301.19 (GPIO14); also elsewhere on the board
GPIO_CHA_P15: A301.20 (GPIO15); also elsewhere on the board
GPIO_CHB_P2: U301.18 (B1); also elsewhere on the board
GPIO_CHB_P3: U301.16 (B3); also elsewhere on the board
GPIO_CHB_P4: U301.14 (B5); also elsewhere on the board
GPIO_CHB_P5: U301.12 (B7); also elsewhere on the board
MEM_CE_N: U301.4 (A3); also elsewhere on the board
MEM_OE_N: U301.2 (A1); also elsewhere on the board
MEM_WE_N: U301.6 (A5); also elsewhere on the board
unnamed: R301.1, U301.1 (DIR), U302.1 (DIR), U303.1 (DIR)
PICO_RESET_N: A301.30 (RUN); also elsewhere on the board
TRIG: J301.2, R302.1; also elsewhere on the board

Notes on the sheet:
Pi PICO Channel A
